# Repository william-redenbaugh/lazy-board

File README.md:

# Teensy Based Macro Board with RGB LEDs and a TFT LCD Display

## Build of Materials:(Work in progress) 
- Teensy 4.0
- SSD1351 128x128 1.5in OLED display
- WS2813 RGB LEDs
- Keycaps TBD
- Keyswitches TBD
- PCB TBD

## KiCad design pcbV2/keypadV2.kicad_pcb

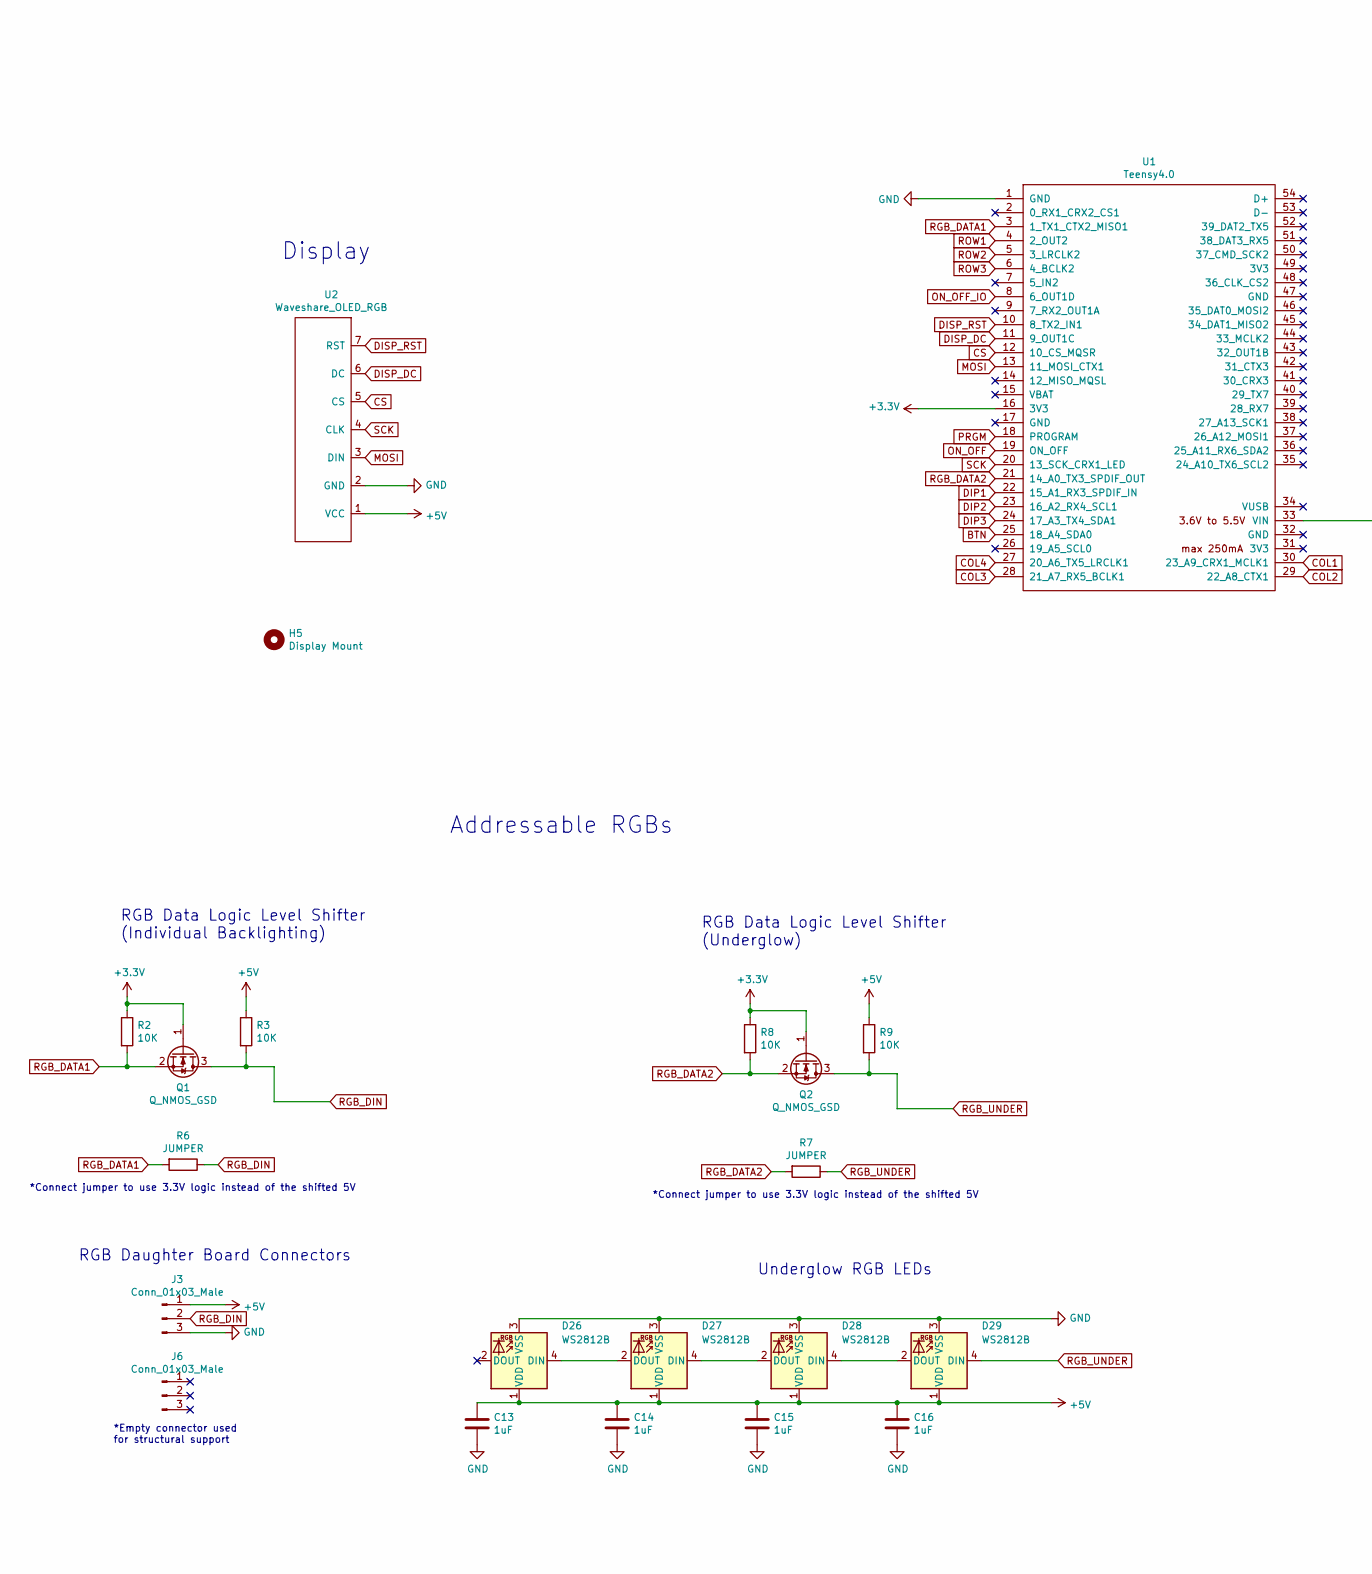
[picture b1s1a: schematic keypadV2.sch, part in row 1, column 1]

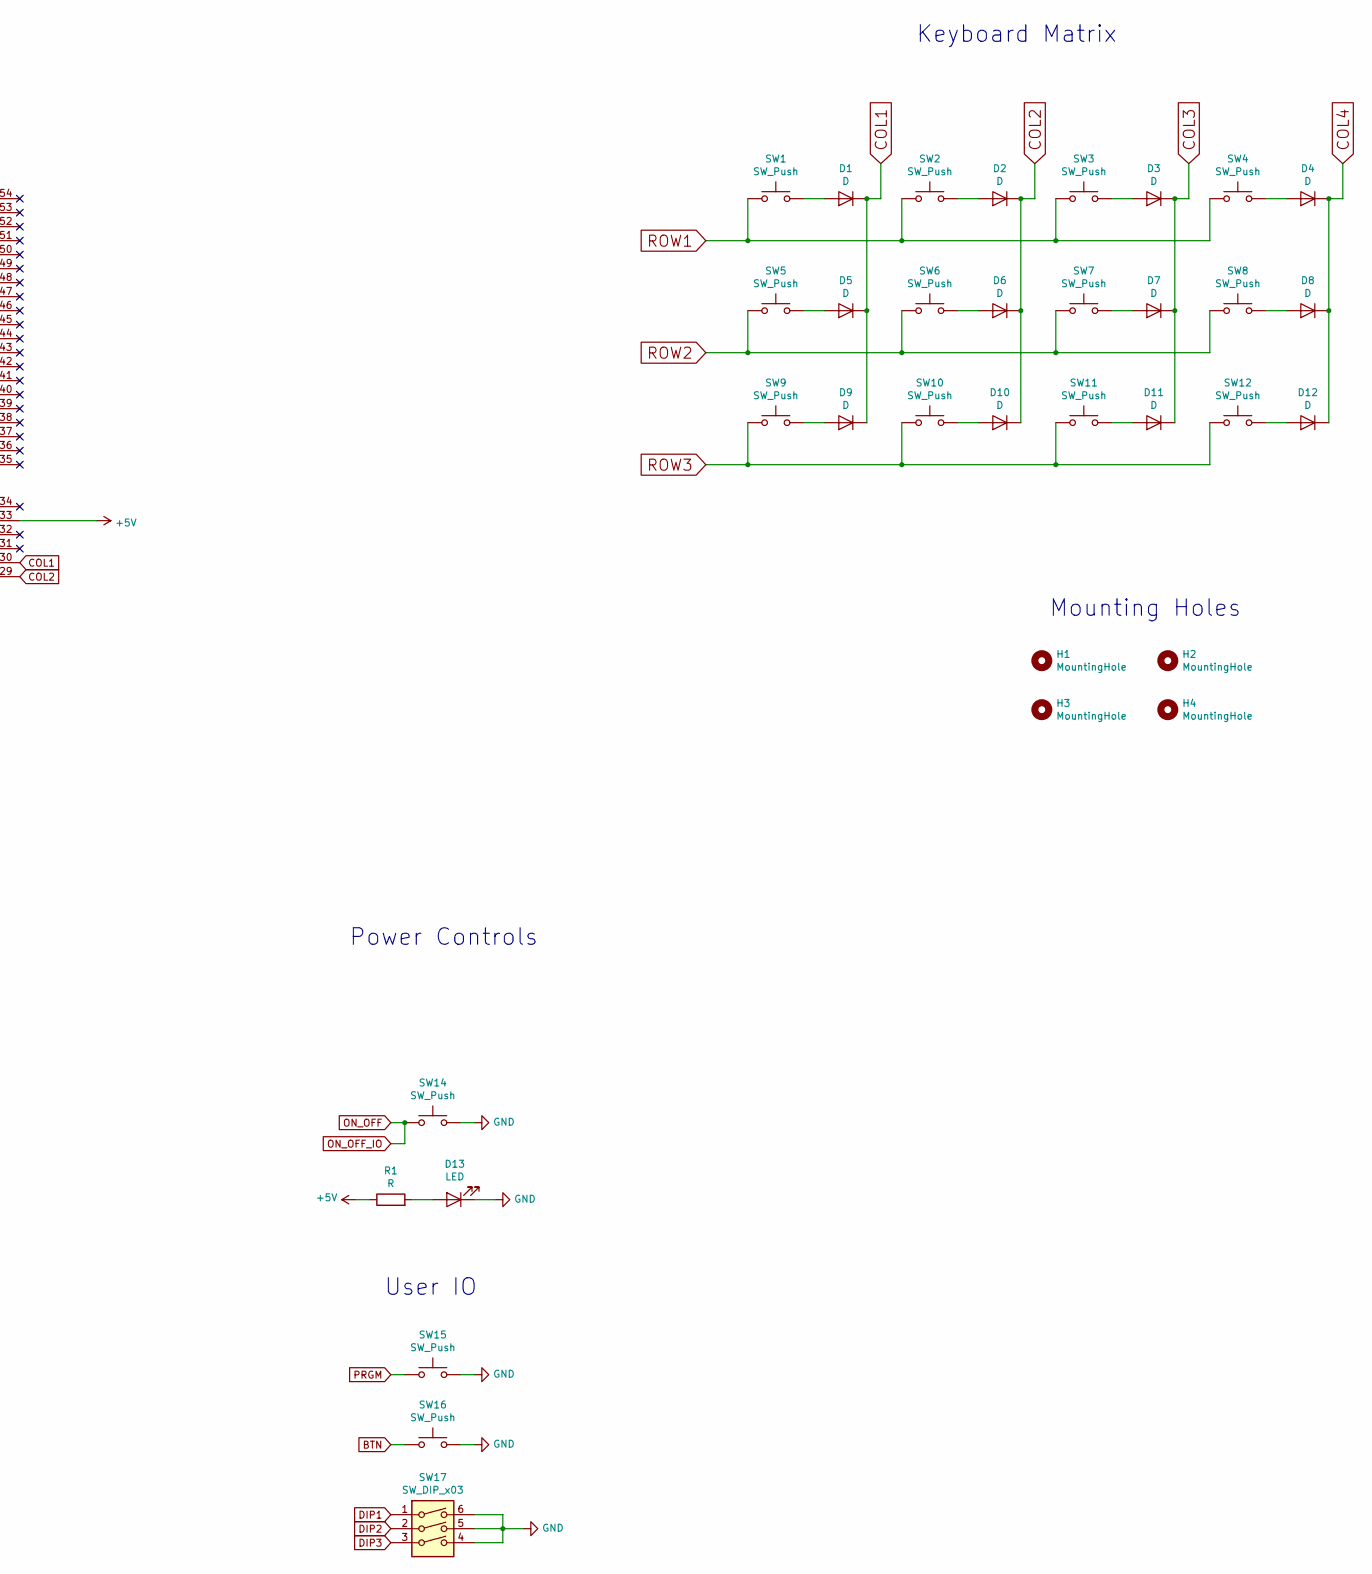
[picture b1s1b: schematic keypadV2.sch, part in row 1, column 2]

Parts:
C13, C14, C15, C16: 1uF; C_1206_3216Metric_Pad1.42x1.75mm_HandSolder
D1, D2, D3, D4, D5, D6, D7, D8, D9, D10, D11, D12: D; D_SOD-323_HandSoldering
D13: LED; LED_1206_3216Metric_Pad1.42x1.75mm_HandSolder
D26, D27, D28, D29: WS2812B; LED_WS2812B_PLCC4_5.0x5.0mm_P3.2mm
H1, H2, H3, H4: MountingHole; MountingHole_3.2mm_M3
H5: Display Mount; Waveshare_LCD_mount V2
J3: Conn_01x03_Male; PinHeader_1x03_P2.54mm_Vertical
J6: Conn_01x03_Male; PinSocket_1x03_P2.54mm_Vertical
Q1, Q2: Q_NMOS_GSD; SOT-23
R1: R; R_1206_3216Metric_Pad1.42x1.75mm_HandSolder
R2, R3, R8, R9: 10K; R_1206_3216Metric_Pad1.42x1.75mm_HandSolder
R6, R7: JUMPER; R_1206_3216Metric_Pad1.42x1.75mm_HandSolder
SW1, SW2, SW3, SW4, SW5, SW6, SW7, SW8, SW9, SW10, SW11, SW12: SW_Push; Kailh_socket_MX
SW14, SW15, SW16: SW_Push; BTN_B3S-1000P
SW17: SW_DIP_x03; DIP3_219-3MSTR
U1: Teensy4.0; Teensy40_REDUCED_PINS
U2: Waveshare_OLED_RGB; PinHeader_1x07_P2.54mm_Vertical

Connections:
+3V3: Q1.1 (G), Q2.1 (G), R2.1, R8.1, U1.16 (3V3)
+5V: C13.1, C14.1, C15.1, C16.1, D26.1 (VDD), D27.1 (VDD), D28.1 (VDD), D29.1 (VDD), J3.1, R1.1, R3.1, R9.1, U1.33 (VIN), U2.1 (VCC)
BTN: SW16.1, U1.25 (18_A4_SDA0)
COL1: D1.1 (K), D5.1 (K), D9.1 (K), U1.30 (23_A9_CRX1_MCLK1)
COL2: D2.1 (K), D6.1 (K), D10.1 (K), U1.29 (22_A8_CTX1)
COL3: D3.1 (K), D7.1 (K), D11.1 (K), U1.28 (21_A7_RX5_BCLK1)
COL4: D4.1 (K), D8.1 (K), D12.1 (K), U1.27 (20_A6_TX5_LRCLK1)
CS: U1.12 (10_CS_MQSR), U2.5 (CS)
DIP1: SW17.1, U1.22 (15_A1_RX3_SPDIF_IN)
DIP2: SW17.2, U1.23 (16_A2_RX4_SCL1)
DIP3: SW17.3, U1.24 (17_A3_TX4_SDA1)
DISP_DC: U1.11 (9_OUT1C), U2.6 (DC)
DISP_RST: U1.10 (8_TX2_IN1), U2.7 (RST)
GND: C13.2, C14.2, C15.2, C16.2, D13.1 (K), D26.3 (VSS), D27.3 (VSS), D28.3 (VSS), D29.3 (VSS), J3.3, SW14.2, SW15.2, SW16.2, SW17.4, SW17.5, SW17.6, U1.1 (GND), U2.2 (GND)
MOSI: U1.13 (11_MOSI_CTX1), U2.3 (DIN)
unnamed: D1.2 (A), SW1.2
unnamed: D2.2 (A), SW2.2
unnamed: D3.2 (A), SW3.2
unnamed: D4.2 (A), SW4.2
unnamed: D5.2 (A), SW5.2
unnamed: D6.2 (A), SW6.2
unnamed: D7.2 (A), SW7.2
unnamed: D8.2 (A), SW8.2
unnamed: D9.2 (A), SW9.2
unnamed: D10.2 (A), SW10.2
unnamed: D11.2 (A), SW11.2
unnamed: D12.2 (A), SW12.2
unnamed: D13.2 (A), R1.2
unnamed: D26.4 (DIN), D27.2 (DOUT)
unnamed: D27.4 (DIN), D28.2 (DOUT)
unnamed: D28.4 (DIN), D29.2 (DOUT)
ON_OFF: SW14.1, U1.8 (6_OUT1D), U1.19 (ON_OFF)
PRGM: SW15.1, U1.18 (PROGRAM)
RGB_DATA1: Q1.2 (S), R2.2, R6.2, U1.3 (1_TX1_CTX2_MISO1)
RGB_DATA2: Q2.2 (S), R7.2, R8.2, U1.21 (14_A0_TX3_SPDIF_OUT)
RGB_DIN: J3.2, Q1.3 (D), R3.2, R6.1
RGB_UNDER: D29.4 (DIN), Q2.3 (D), R7.1, R9.2
ROW1: SW1.1, SW2.1, SW3.1, SW4.1, U1.4 (2_OUT2)
ROW2: SW5.1, SW6.1, SW7.1, SW8.1, U1.5 (3_LRCLK2)
ROW3: SW9.1, SW10.1, SW11.1, SW12.1, U1.6 (4_BCLK2)
SCK: U1.20 (13_SCK_CRX1_LED), U2.4 (CLK)

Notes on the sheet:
User IO
Power Controls
Display
Addressable RGBs
RGB Data Logic Level Shifter (Individual Backlighting)
*Connect jumper to use 3.3V logic instead of the shifted 5V
RGB Daughter Board Connectors
Keyboard Matrix
Underglow RGB LEDs
RGB Data Logic Level Shifter (Underglow)
*Empty connector used for structural support
Mounting Holes

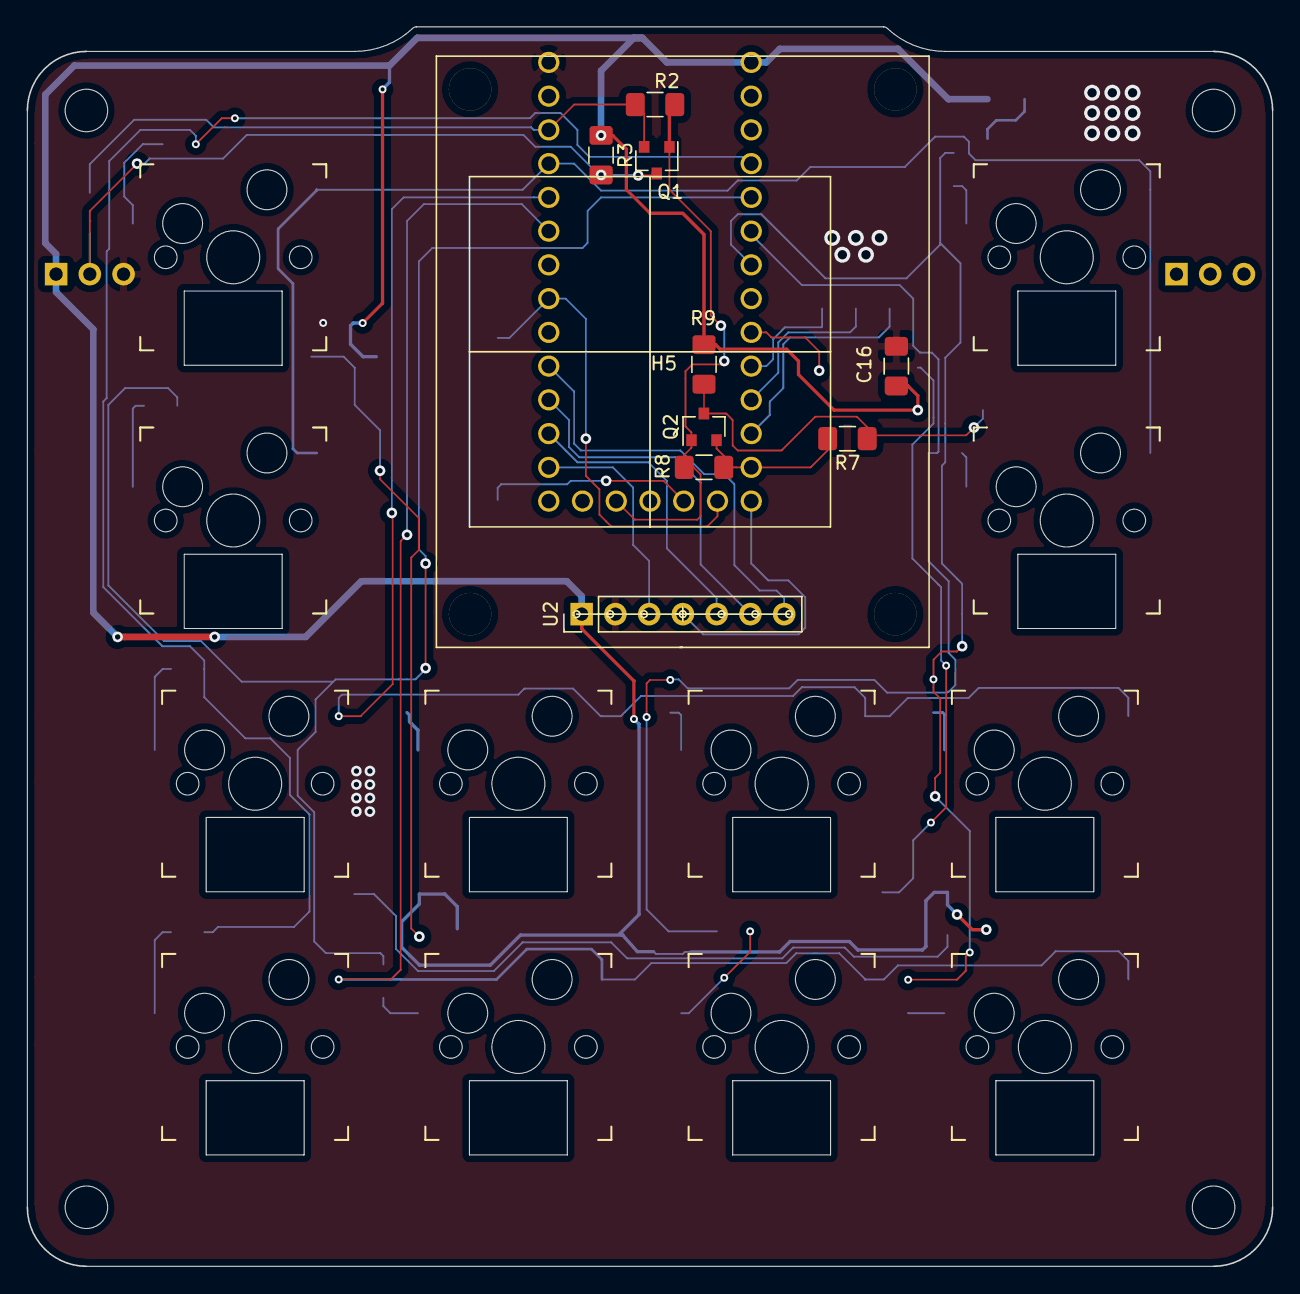
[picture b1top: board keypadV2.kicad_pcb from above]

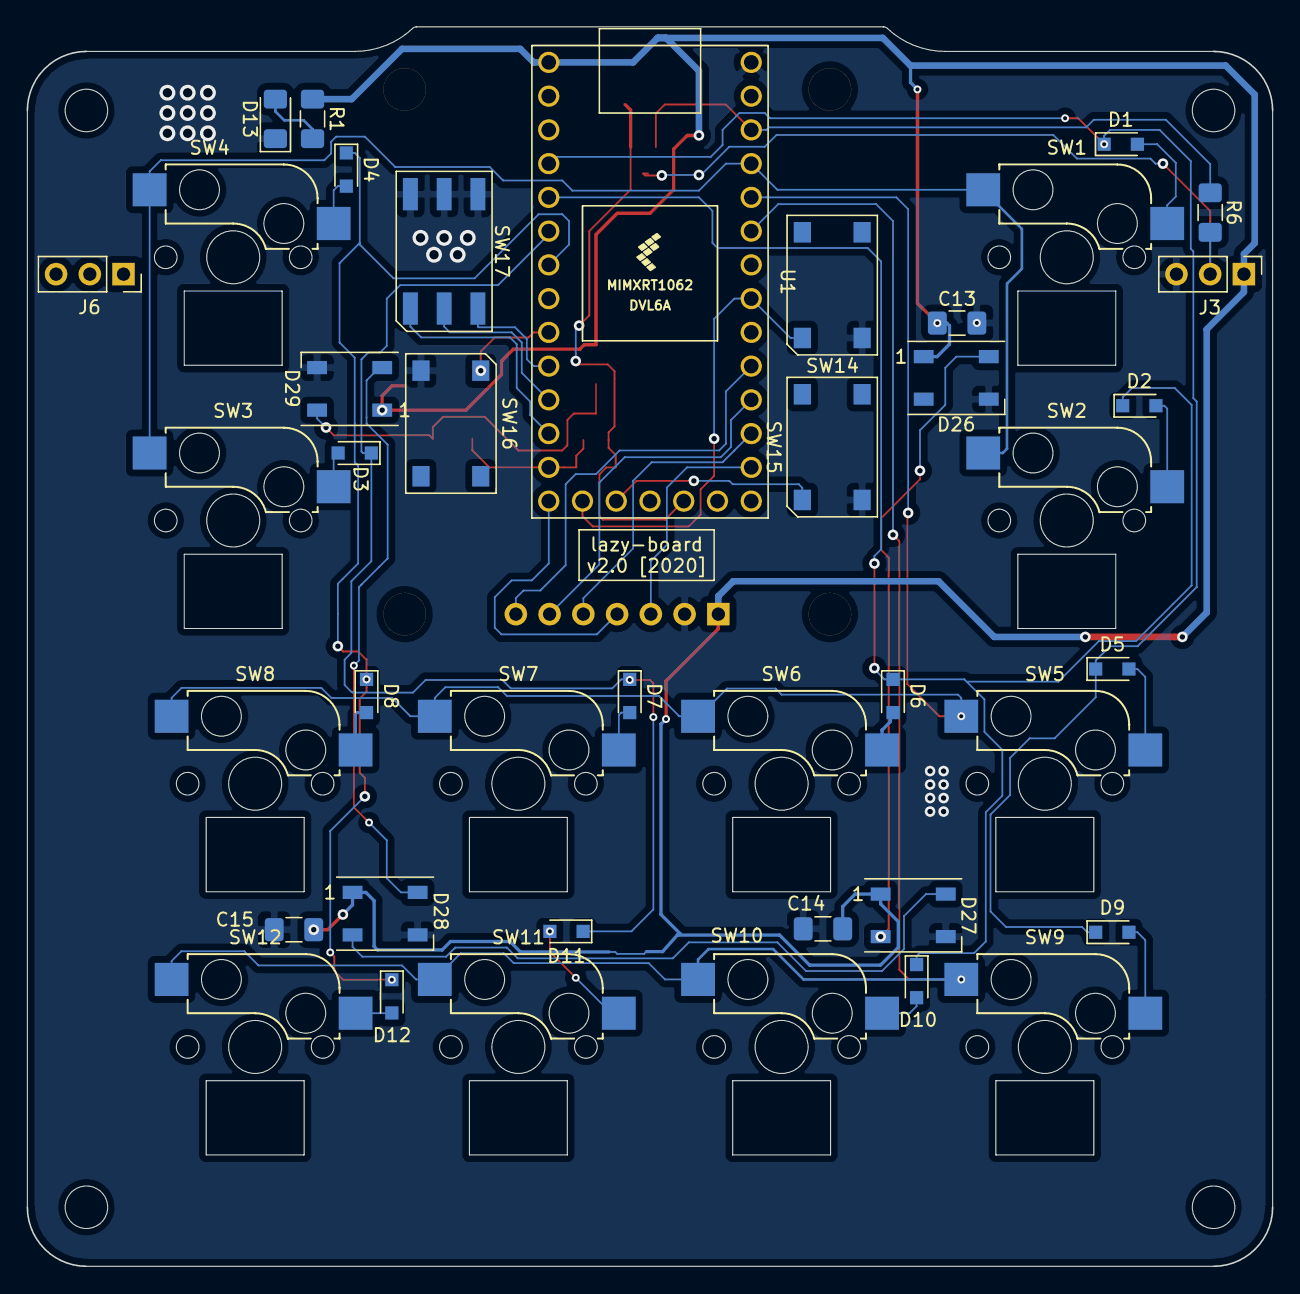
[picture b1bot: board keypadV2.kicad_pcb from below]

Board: 2 copper layers, 93.7 x 93.3 mm, 55 parts (28 on the bottom side), 41 nets.

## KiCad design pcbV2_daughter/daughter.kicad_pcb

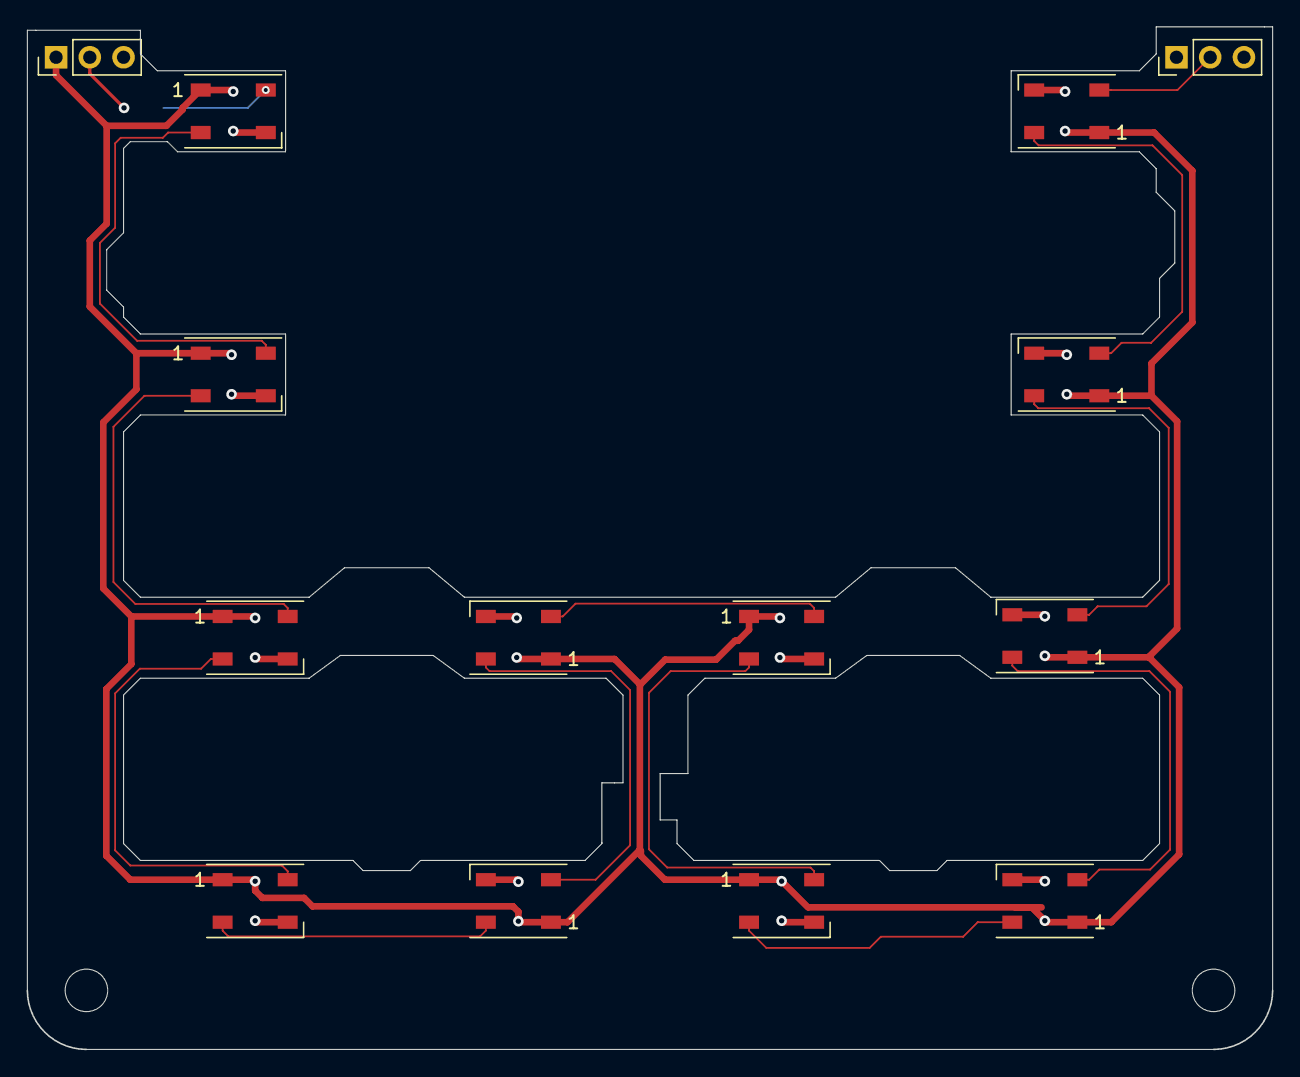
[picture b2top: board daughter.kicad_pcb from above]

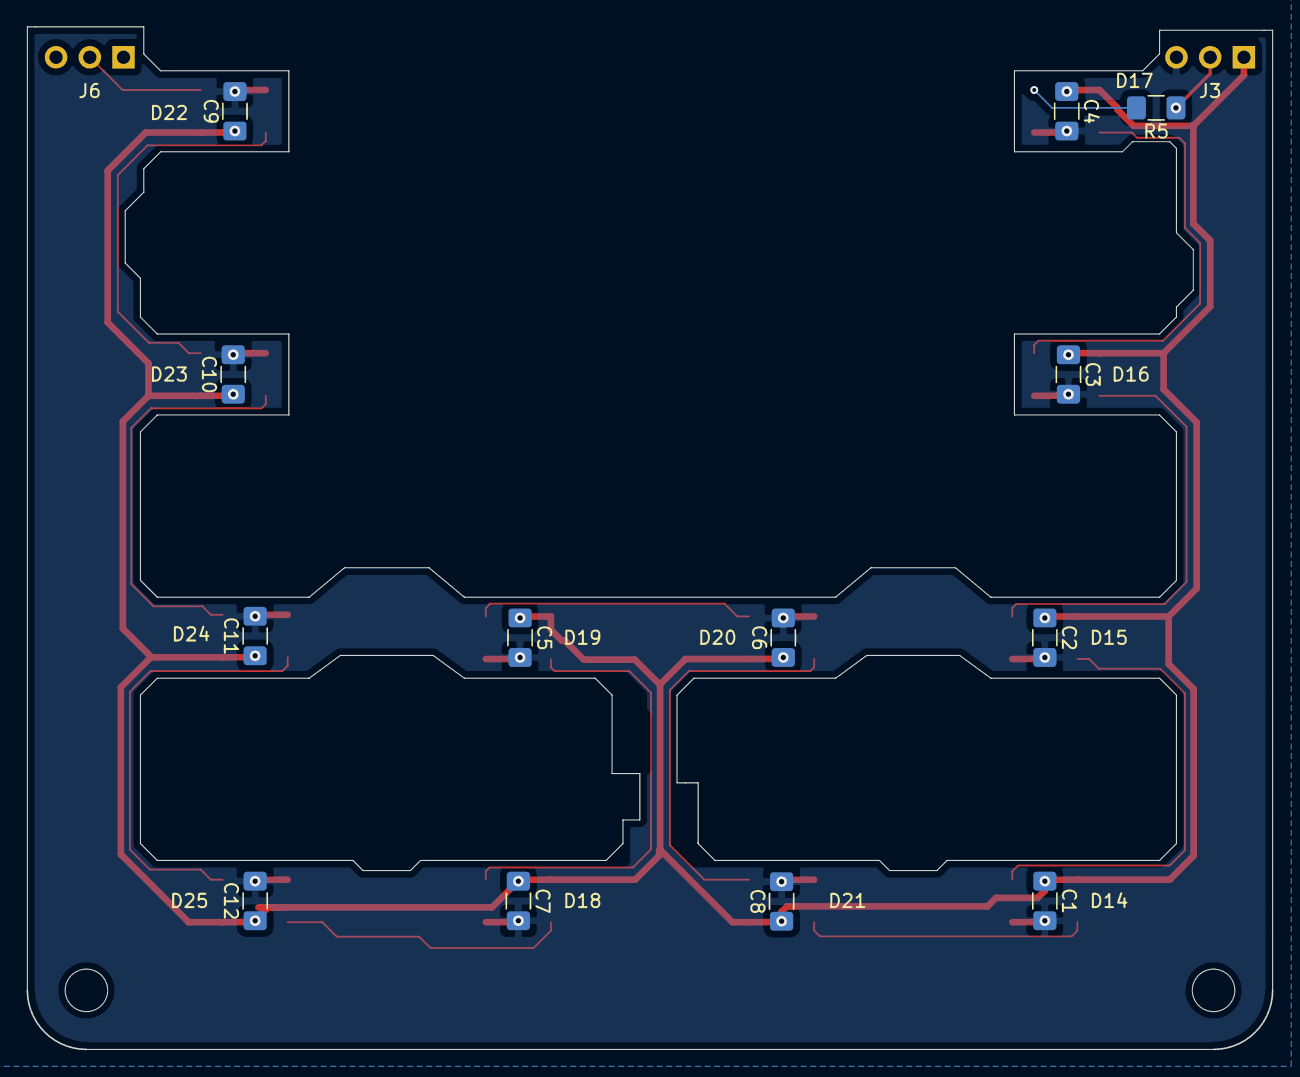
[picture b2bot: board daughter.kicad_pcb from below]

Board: 2 copper layers, 93.7 x 77.0 mm, 27 parts (13 on the bottom side), 16 nets.

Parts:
C1, C2, C3, C4, C5, C6, C7, C8, C9, C10, C11, C12: 1000uF; C_1206_3216Metric_Pad1.42x1.75mm_HandSolder
D14, D15, D16, D17, D18, D19, D20, D21, D22, D23, D24, D25: WS2812B; LED_WS2812B_PLCC4_5.0x5.0mm_P3.2mm
J3, J6: Conn_01x03_Male; PinHeader_1x03_P2.54mm_Vertical
R5: R_DIN; R_1206_3216Metric_Pad1.42x1.75mm_HandSolder

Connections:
+5V: C1.1, C2.1, C3.1, C4.1, C5.1, C6.1, C7.1, C8.1, C9.1, C10.1, C11.1, C12.1, D14.1, D15.1, D16.1, D17.1, D18.1, D19.1, D20.1, D21.1, D22.1, D23.1, D24.1, D25.1, J3.1
GND: C1.2, C2.2, C3.2, C4.2, C5.2, C6.2, C7.2, C8.2, C9.2, C10.2, C11.2, C12.2, D14.3, D15.3, D16.3, D17.3, D18.3, D19.3, D20.3, D21.3, D22.3, D23.3, D24.3, D25.3, J3.3
unnamed: D14.2, D21.4
unnamed: D14.4, D15.2
unnamed: D15.4, D16.2
unnamed: D16.4, D17.2
unnamed: D17.4, R5.1
unnamed: D18.2, D25.4
unnamed: D18.4, D19.2
unnamed: D19.4, D20.2
unnamed: D20.4, D21.2
unnamed: D22.4, D23.2
unnamed: D23.4, D24.2
unnamed: D24.4, D25.2
RGB_DIN: J3.2, R5.2
RGB_DOUT: D22.2, J6.2

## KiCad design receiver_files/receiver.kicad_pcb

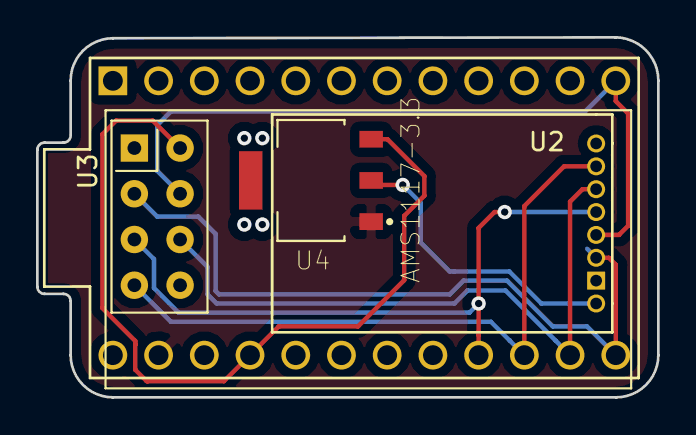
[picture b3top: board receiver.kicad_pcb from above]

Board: 2 copper layers, 34.5 x 20.0 mm, 4 parts (1 on the bottom side), 8 nets.

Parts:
U1: ProMicro
U2: NRF24L01_Breakout; NR24l01mini
U3: NRF24L01_Breakout; nRF24L01_Breakout
U4: AMS1117-3.3; SOT229P700X180-4N

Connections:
/3.3V: U2.2, U4.2
/GND1: U1.23, U2.1, U3.1, U4.1
/VCC1: U1.21, U3.2, U4.3
unnamed: U1.12, U2.4, U3.4
unnamed: U1.13, U2.3, U3.3
unnamed: U1.14, U2.6, U3.6
unnamed: U1.15, U2.7, U3.7
unnamed: U1.16, U2.5, U3.5

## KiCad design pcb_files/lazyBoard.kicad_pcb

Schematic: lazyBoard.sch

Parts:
BT1: Battery_Cell; PinHeader_1x02_P2.54mm_Vertical
D1, D2, D3, D4, D5, D6, D7, D8, D9, D10, D11, D12, D13, D14, D15, D16: D; D_SOD123_axial_noSMD
D20, D21, D22, D23, D24, D25, D26, D27, D28, D29, D30, D31, D32, D33, D34, D35: LED; C_3528v1
J1, J2: AudioJack3_Ground; CUI_SJ-43514-SMT
K1, K2, K3, K4, K5, K6, K7, K8, K9, K10, K11, K12, K13, K14, K15, K16: KEYSW; PG1350_socket
R1, R2, R3: R; D_SOD123_axial
U1: ProMicro; ProMicroPinsFlipped
U2: NRF24L01_Breakout; nrf24l01header
U3, U5, U6: ADG417BN; PinHeader_1x03_P2.54mm_Vertical
U4: AMS1117-3.3; SOT229P700X180-4N
U7: TLC5940PWP; HTSSOP-28-1EP_4.4x9.7mm_P0.65mm_EP3.4x9.5mm_Mask2.4x6.17mm_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

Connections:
/Col1: K1.1, K5.1, K9.1, K13.1, U1.7 (D4)
/Col2: K2.1, K6.1, K10.1, K14.1, U1.1 (TX)
/Col3: K3.1, K7.1, K11.1, K15.1, U1.9 (D7)
/Col4: K4.1, K8.1, K12.1, K16.1, U1.20 (F4)
/GND1: BT1.2 (-), J1.4, J2.4, R3.1, U1.23 (GND), U2.1 (GND), U4.1, U7.1, U7.6
/GSCLK: U1.8 (C6), U7.25
/RAW1: J2.3, U1.24 (RAW), U3.2 (NC)
/Row1: D1.1 (K), D2.1 (K), D3.1 (K), D4.1 (K), U1.10 (E6)
/Row2: D5.1 (K), D6.1 (K), D7.1 (K), D8.1 (K), U1.11 (B4)
/Row3: D9.1 (K), D10.1 (K), D11.1 (K), D12.1 (K), U1.2 (RX)
/Row4: D13.1 (K), D14.1 (K), D15.1 (K), D16.1 (K), U1.19 (F5)
/VCC1: D20.1, D21.1, D22.1, D23.1, D24.1, D25.1, D26.1, D27.1, D28.1, D29.1, D30.1, D31.1, D32.1, D33.1, D34.1, D35.1, J1.3, U1.21 (VCC), U5.1, U6.2 (NC), U7.26, U7.28
unnamed: BT1.1 (+), U3.3 (GND)
unnamed: D1.2 (A), K1.2
unnamed: D2.2 (A), K2.2
unnamed: D3.2 (A), K3.2
unnamed: D4.2 (A), K4.2
unnamed: D5.2 (A), K5.2
unnamed: D6.2 (A), K6.2
unnamed: D7.2 (A), K7.2
unnamed: D8.2 (A), K8.2
unnamed: D9.2 (A), K9.2
unnamed: D10.2 (A), K10.2
unnamed: D11.2 (A), K11.2
unnamed: D12.2 (A), K12.2
unnamed: D13.2 (A), K13.2
unnamed: D14.2 (A), K14.2
unnamed: D15.2 (A), K15.2
unnamed: D16.2 (A), K16.2
unnamed: D20.2, U7.22
unnamed: D21.2, U7.21
unnamed: D22.2, U7.20
unnamed: D23.2, U7.19
unnamed: D24.2, U7.18
unnamed: D25.2, U7.17
unnamed: D26.2, U7.16
unnamed: D27.2, U7.15
unnamed: D28.2, U7.14
unnamed: D29.2, U7.13
unnamed: D30.2, U7.12
unnamed: D31.2, U7.11
unnamed: D32.2, U7.10
unnamed: D33.2, U7.9
unnamed: D34.2, U7.8
unnamed: D35.2, U7.7
unnamed: J1.1, J2.1, R2.1, U1.5 (SCL)
unnamed: J1.2, J2.2, R1.1, U1.6 (SDA)
unnamed: R1.2, R2.2, U5.2 (NC)
unnamed: R3.2, U7.27
unnamed: U1.12 (B5), U7.3
unnamed: U1.13 (B6), U7.2
unnamed: U1.14 (B2), U2.6 (MOSI), U7.5
unnamed: U1.15 (B3), U2.7 (MISO)
unnamed: U1.16 (B1), U2.5 (SCK), U7.4
unnamed: U1.17 (F7), U2.4 (~CSN)
unnamed: U1.18 (F6), U2.3 (CE)
unnamed: U2.2 (VCC), U4.2
unnamed: U4.3, U6.3 (GND)

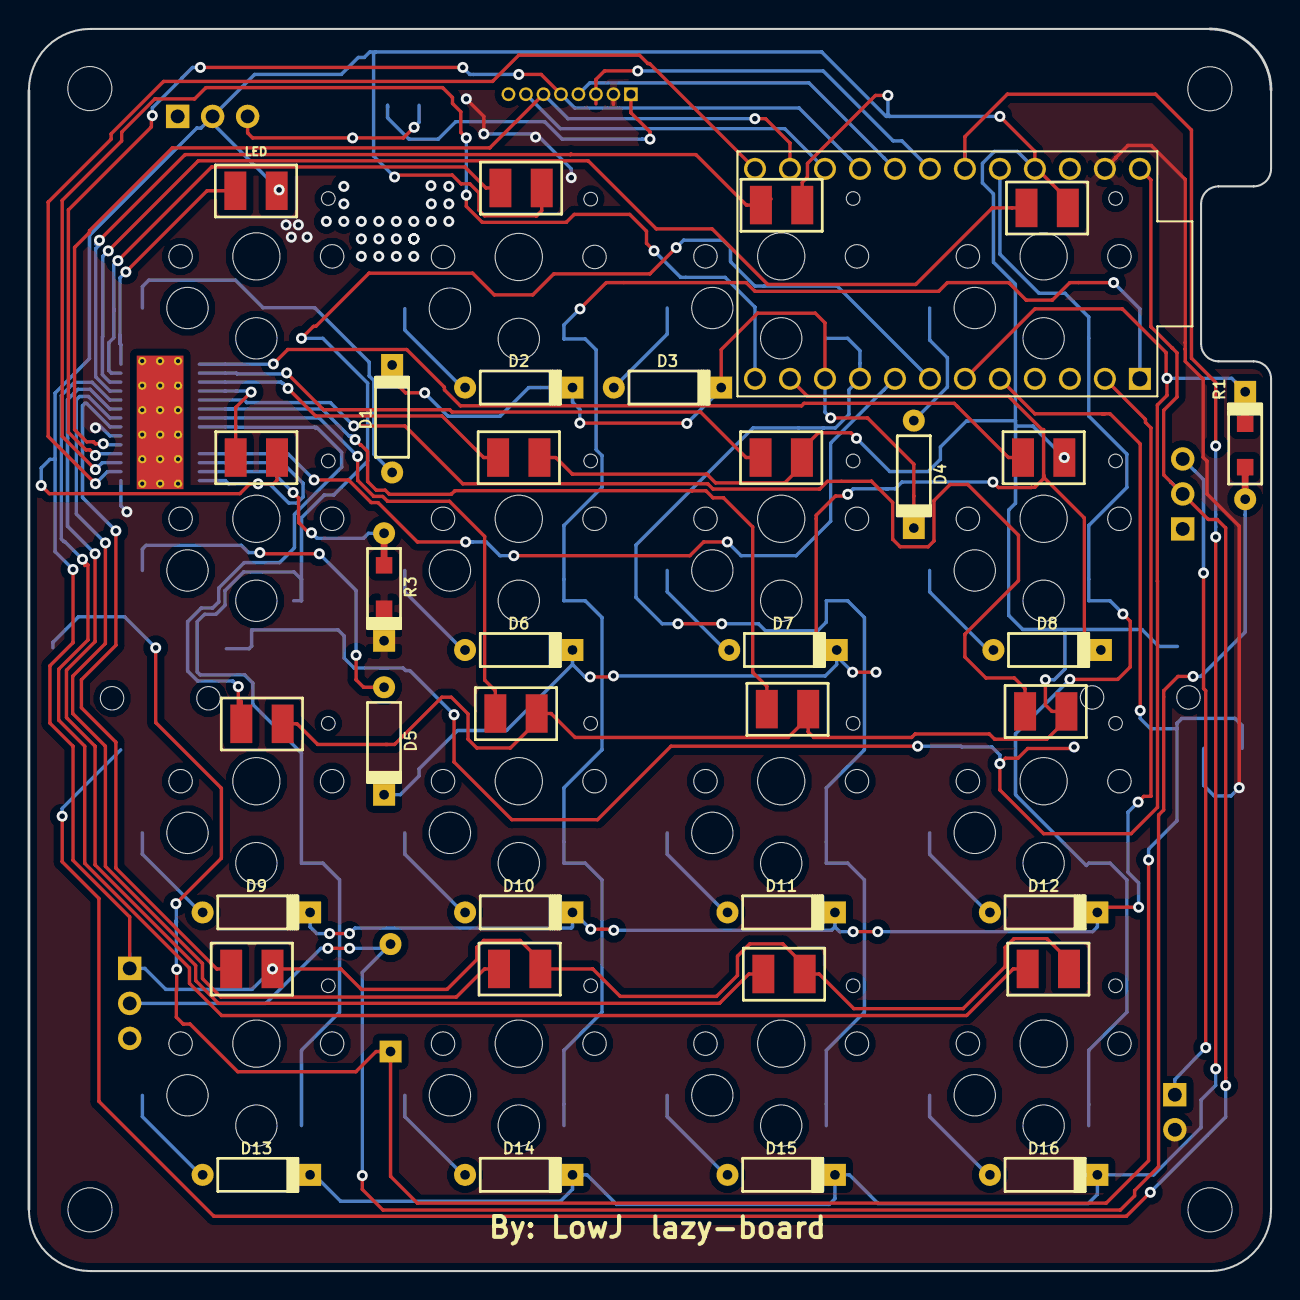
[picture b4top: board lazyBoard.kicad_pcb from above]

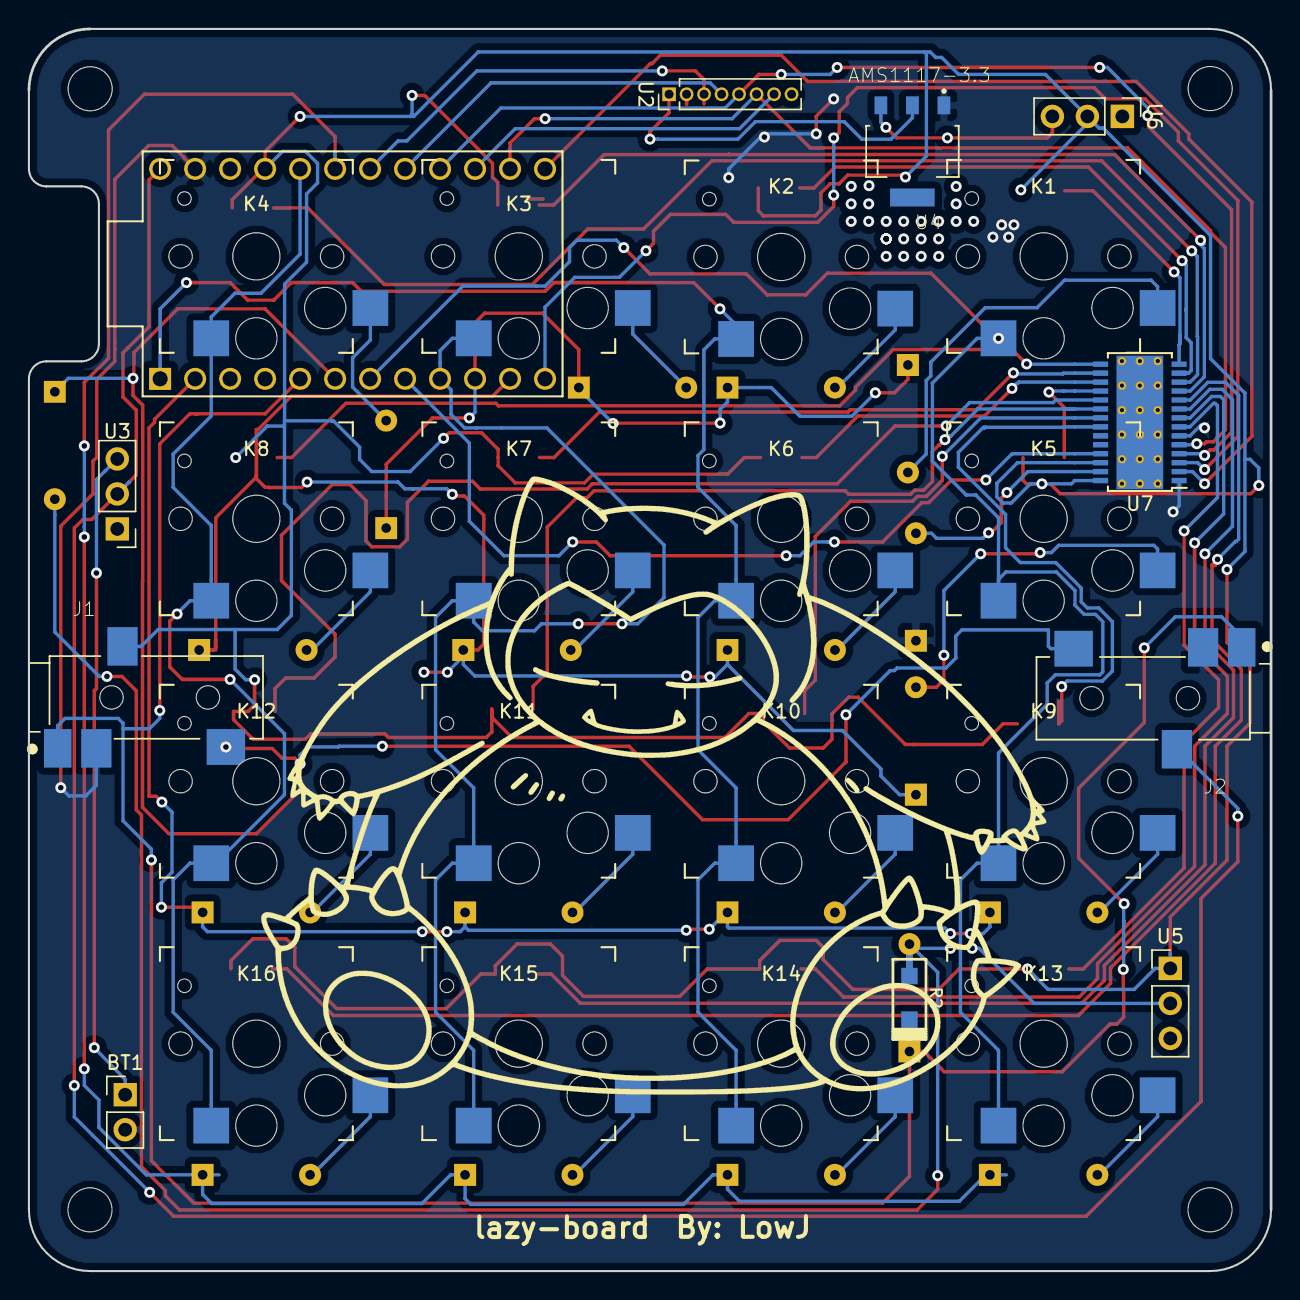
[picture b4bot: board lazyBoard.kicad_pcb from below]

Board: 2 copper layers, 90.2 x 90.2 mm, 61 parts (10 on the bottom side), 58 nets.

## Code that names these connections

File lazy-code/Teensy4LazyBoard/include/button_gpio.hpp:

/*
Author: William Redenbaugh
Last Edit Date: 7/3/2020
*/

#ifndef _BUTTON_GPIO_HPP
#define _BUTTON_GPIO_HPP

#include "Arduino.h"
#include "ChRt.h"
#include "lwip_thread.hpp"

#define DIP1 17
#define DIP2 16
#define DIP3 15
#define BUTTON 14

extern void setup_dip_button(void);
#endif 

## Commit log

2019-02-11 added ground plane
2019-02-11 added cu ground plane
2019-02-13 added status led
2019-02-13 added drill holes
2019-02-13 added wired communication between boards
2019-02-15 final v1
2019-03-21 added code
2019-03-21 added comments to code
2019-03-24 started reworking board
2019-03-24 updated schem
2019-04-04 switch and diode pcb layout
2019-04-04 layed out components
2019-04-04 flipped the position of nrf24l01
2019-04-08 start tracing
2019-04-12 added traces to key matrix
2019-04-18 ldo heat sink and edge cuts
2019-04-19 started led matrix
2019-04-25 TLC5940 LED controller
2019-04-27 traces from led ic
2019-04-27 matrix and nrf24l01 traces
2019-04-28 finished traces
2019-04-30 adding TLC5940 connections
2019-05-01 reworked led wiring
2019-05-01 cleaned up traces
2019-05-02 cleaned up board text
2019-05-02 cleand up traces
2019-05-02 add pcb for receiver
2019-05-17 pcb sent to print
2019-05-21 updated code for 4x4 and LED matrix
2019-05-22 added a wave pattern
2019-05-24 Added housing files for laser cutting
2019-05-28 housing CAD v1
2019-05-28 dwg files for houisng
2019-05-28 added dwg files
2019-05-29 added v2 of housing
2019-06-04 created a new lighting pattern
2019-06-05 finished code
2019-06-05 reverted pcb_files
2019-06-22 added image for pcb
2019-06-23 snorlax in silk screen
2019-06-24 fixed unconnected grounds
2019-06-25 re added mounting holes
2019-06-25 renamed project
2019-08-05 updated housing
2019-08-05 Layer5 better fit
2019-08-10 modified casing, #2 holes
2019-08-10 updated housing layer 4
2019-08-12 updated casing
2020-06-07 Setup Teensy Dev environment with ChibiOS
2020-06-08 set pin denominations and created thread and stack space for all of our runtime threads
2020-06-08 setup led strip code
2020-06-08 added support for protobuffers and some example messages
2020-06-09 integrated basic keyboard macro functionality into a specific thread, setup led strip stuff, added doxygen comments, implement keyboard gpio
2020-06-09 moved over data serialization and deserialization code over
2020-06-10 Revert "mm"
    This reverts commit 577ec9d6cdd566b4086e94dff4a681b290f74ba2.
2020-06-10 Fixing issues.
2020-06-11 began testing with UART DMA for LED strips
2020-06-11 Moved led matrix stuff into it's own module for easier modularity.
2020-06-11 Binded LEDs to Macros and fixed led matrix function. Added HSV support.
2020-06-12 made some changes, fixed grammar, enabled display thread
2020-06-12 Some fixes and updates
    -Fixed typo in rgb -> hsv conversion for led matrix.
2020-06-12 Started integrating animationns into led matrix stuf.
    yea that about sums it up lol.
2020-06-12 changed readme, started dev on spi based lcd
2020-06-12 added adafruit gfx to gitmodules
2020-06-12 I'm tired
2020-06-12 Validated both serial communication and keyboard communication working at the same time
    after I've validated that both parts of the software work, can now start developing other parts of the project.
2020-06-13 moved files over to include folder
2020-06-13 starting working with chibiOS mutexes and signals
2020-06-14 Update hsv_rgb_conv.hpp
    changed from unsigned char to uint8_t
2020-06-15 Added thread signaling for key animations to matrix, started debugging keyboard matrix code.
2020-06-16 removed nanopb files
2020-06-16 moved nanopb into submodule
2020-06-17 properly fixed ghosting issues with keyboard, changed the keyboard macros to the relevant ones, modified the LCD librariy, started working on the reactive animations for led runtime
2020-06-17 refined reactive matrix code
2020-06-17 fixed final issues regarding reactive lighting
2020-06-17 final -push- to master branch without real code review, finally got project to a working state, will update on -feature- branches from here on out
2020-06-18 started development on protobuffer messaging
2020-06-18 implemented communication for dealing with keybinding information
2020-06-18 fixed macro binding for protobuffers, added up to 16 macro keys, completed (unsafe) reprogramming of macro keys
2020-06-19 finished enumerated key conversions to actual key values in the teensy, implemented
2020-06-19 completed basic integration of protobuffers with RGB LED animations
2020-06-19 changed to different display module, updated gitmodules
2020-06-20 testing led matrix
2020-06-20 removing ssd1351 library
2020-06-20 started changing how we are going to deal with animations on the LCD display
2020-06-21 updating gitmodules and stuff in submodules
2020-06-22 moved over OLED code from adafruit library into our own library, setup propper DMA buffering so we can have nice smooth fps
2020-06-22 moved stuff to prevent submodule errors, added documentation to new led library, added set rotation feature, fixed color bit length issues
2020-06-22 Started working on testing for board, implemented a bunch of fast math stuff, improved spi display runtime, fixed sleep mode, slight changes to macros
2020-06-22 added some documentation, allowed the ability to save keymaps to eeprom
2020-06-23 removed SSID1351 library since we aren't using it anymore
2020-06-25 Started Altiumboard
2020-06-25 Added basic IO, switches, buttons, USBC, to schem
2020-06-26 Schematic v1
2020-06-26 PDF added notes to schematic
2020-06-26 Added notes and LEDs for underglow
2020-06-26 updated project pdf
2020-06-26 save changes
2020-06-26 started switch footprint, double check measurements
2020-06-26 save
2020-06-26 rgb_data now on pin 1
2020-06-26 added pcb stuff
2020-06-26 started changing gpio stuff
2020-06-26 added a couple gitmodules
2020-06-26 chaged file stucture
2020-06-27 Added footprint libraries
2020-06-27 started new schem in KiCAD
2020-06-27 start mapping symbols and footprints
2020-06-27 added a picture for the readme
2020-06-27 Added picture to readme
2020-06-27 changed teensy 4 clock speed since we G O T T A G O F A S T
2020-06-27 start pcb layout
2020-06-27 remade teensy footprint
2020-06-28 basic layout v1
2020-06-28 created footprint for lcd
2020-06-28 add update
2020-06-28 edge cuts
2020-06-28 added ws2812b cutouts
2020-06-28 started layout of daughterboard
2020-06-28 component layout v1
2020-06-28 Start daughterboard
2020-06-29 finished v1 of daughter board
2020-06-29 Updated schematic on mainboard, LEDs moved to daughter board
2020-06-29 added mouting holes
2020-06-29 Updated schematic to use seperate RGB Data pin for underglow LEDs
2020-06-29 Added components for 2nd RGB Data line
2020-06-29 Started laying traces
2020-06-30 3.3V was on wrong pin on teens
2020-06-30 finished tracing
2020-06-30 updated pcb
2020-06-30 updates for tonight
2020-06-30 added support for the underglow lighting
2020-06-30 making sure that prototype 0 still works on master branch
2020-06-30 keeping proto 0 working for now
2020-06-30 started working on low priority work thread
2020-07-01 removed usb c
2020-07-01 setup a low priority worker thread that we can assign a bunch of menial tasks to
2020-07-01 added dip switch support
2020-07-01 started rewiring
2020-07-01 v2 layout
2020-07-01 edited layout, updated daughter board
2020-07-01 moved some labels around
2020-07-01 generated plots files
2020-07-01 added the ability to enable, disable and delete threads by handler ID
2020-07-01 added thread safety to the low priority work thread
2020-07-01 added documentation for dip switches
2020-07-02 finished adding thread safety code, fixed SPI dma ram waste usage
2020-07-03 updated gerber files
2020-07-04 moved over lpwork into it's own module
2020-07-04 added signature to the codebase
2020-07-04 added more signatures
2020-07-04 updating daughter board to be more structurally safe
2020-07-05 generated gerber files
2020-07-09 Prototype 1 Code changes (#9)
    * started working on low priority work thread
    * removed usb c
    * setup a low priority worker thread that we can assign a bunch of menial tasks to
    * added dip switch support
    * started rewiring
    * v2 layout
2020-07-16 added adafruit gfx library
2020-07-19 added the ability to flash more images
2020-07-19 allocated more flash space for our images
2020-08-20 changed code to ensure that LEDs work on official pcb, display trigger animations have been changed to just colors rather than triggering characters
2020-08-21 Started port of macropad to Will-OS
2020-08-21 got basic keyboard functionality working on on TeensyOS
2020-08-21 completed keyboard runtime refractor during transision to will-os
2020-08-21 completed refractor of led matrix handler module
2020-08-21 improved matrix cycle individual command
2020-08-22 started implemented messaging between host device and macropad
2020-08-24 slight refractor to keyboard runtime thread along with implementation of reactive ability in matrix runtime
2020-08-25 started working on rust testing code, implementing fading between matrix animations, implemented interrupt driven communication
2020-08-26 various changes
2020-08-28 updated subrepos, started working on frame updates for OLED display
2020-09-02 updated display drivers
2020-09-06 Create LICENSE
2020-09-08 Create LICENSE (#11)
2020-12-07 test swtich slot fort plate
2020-12-07 drafted basic outline for plate
2020-12-07 test print to check outline
2020-12-07 extruded plate 5mm, add notches for switches
2020-12-07 generate stl files
2020-12-09 started outercase
    -Add cutouts for RGB underglow
    -Add holes for m2 inserts
    -Create screen cover
    -Make sure inserts have space under so scre can pass through
    -Cut outs for feet
2020-12-10 made draft for outer housing and screen shield
2020-12-11 created spacer
2020-12-11 outer: rgb slots, fixxed teensy clearence issue, made case fit looser, fixed m2 threaded insert slots
2020-12-28 converts images into an array of rgb565 values. able to display images on oled
2021-02-08 modified outer and shield
2021-02-08 generate stls
2021-12-27 remapped some keys
2022-03-09 made shield longer
2022-03-09 shield extruded supporting part
2022-03-09 generate stl for shield update
2022-03-09 raised pcb mounts by 2mm and raised brim by 2mm so flush with plate
2022-03-09 new spacers
2022-03-10 created lock in version of spacer and stl
2022-03-10 updated plate to have bigger cutouts for daughter board solder joints, this was causing interferance before
2022-03-10 new spacer to support m2 screws
2022-03-10 updated outer
2022-03-11 edits to outer
